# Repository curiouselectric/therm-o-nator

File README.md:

# therm-o-nator
A temperature sensing thermocouple amplifier kit

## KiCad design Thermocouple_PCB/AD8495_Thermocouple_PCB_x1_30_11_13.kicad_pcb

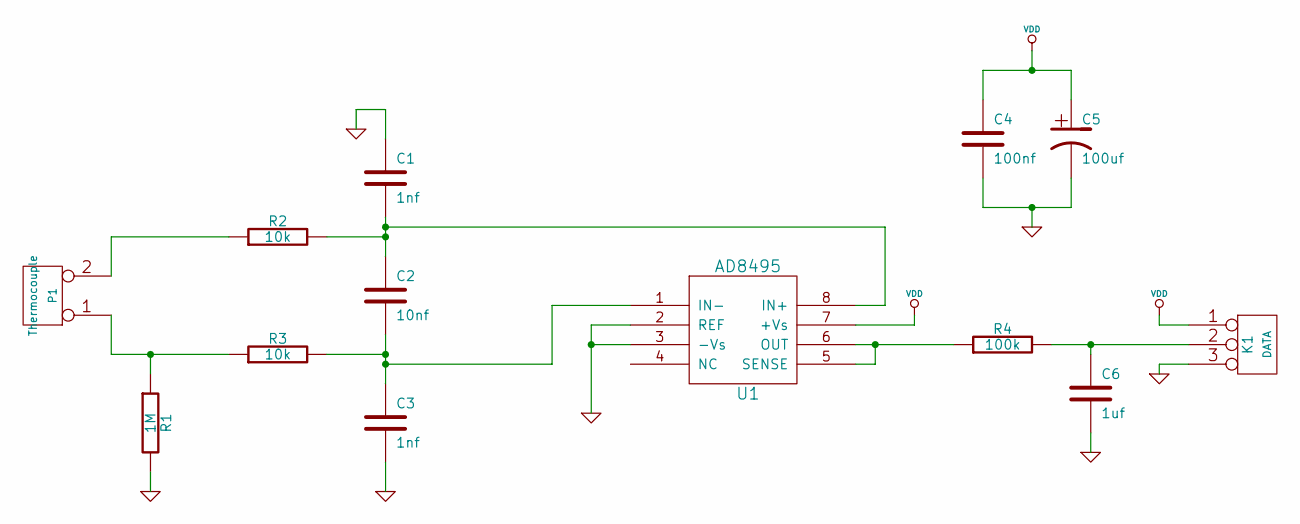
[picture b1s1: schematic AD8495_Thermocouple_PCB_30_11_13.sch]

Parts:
C1, C3: 1nf
C2: 10nf
C4: 100nf
C5: 100uf
C6: 1uf
K1: DATA
P1: Thermocouple
R1: 1M
R2, R3: 10k
R4: 100k
U1: AD8495

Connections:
GND: C1.1, C3.2, C4.2, C5.2, C6.2, K1.3, R1.2, U1.2 (REF), U1.3 (-Vs)
unnamed: C6.1, K1.2 (PM), R4.2
unnamed: R4.1, U1.5 (SENSE), U1.6 (OUT)
unnamed: P1.2 (PM), R2.1
unnamed: P1.1, R1.1, R3.1
unnamed: C2.2, C3.1, R3.2, U1.1 (IN-)
unnamed: C1.2, C2.1, R2.2, U1.8 (IN+)
VDD: C4.1, C5.1, K1.1, U1.7 (+Vs)

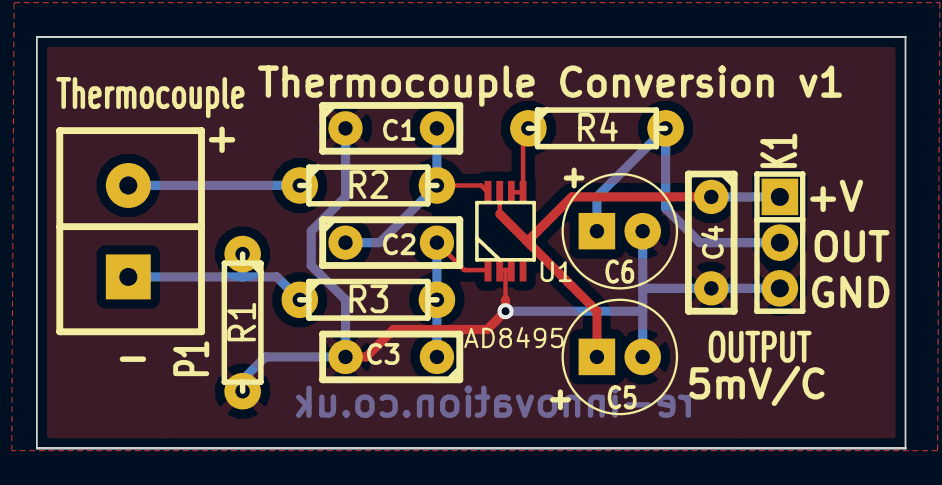
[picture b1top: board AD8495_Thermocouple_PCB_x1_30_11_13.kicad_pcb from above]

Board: 2 copper layers, 48.3 x 22.9 mm, 13 parts (0 on the bottom side), 8 nets.

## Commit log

2015-11-30 Upload of files v1
2015-12-03 Initial files
    2015 12 3
